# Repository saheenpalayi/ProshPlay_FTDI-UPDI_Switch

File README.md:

# ProshPlay_FTDI-UPDI_Switch
## Overview
 I made this breakout board to program the Avr 1 series chips like attiny1614, attiny412. This design have the feature to switch between the FTDI (UART) and UPDI Programming Mods with the help of a FTDI USB to TTL Serial Converter Adapter Module, Checkout the [ProshPlay_CH340G_Type-C_FTDI_Converter](https://github.com/saheenpalayi/ProshPlay_CH340G_Type-C_FTDI_Converter) that I used in this project 

## Schematic

## PCB

## Fabrication

## Testing

Refrences and Links

 - [Arduino Forum - Uploading Program to ATTiny 1616 via Serial UPDI and CH340 programmer](https://forum.arduino.cc/t/uploading-program-to-attiny-1616-via-serial-updi-and-ch340-programmer/1261787)

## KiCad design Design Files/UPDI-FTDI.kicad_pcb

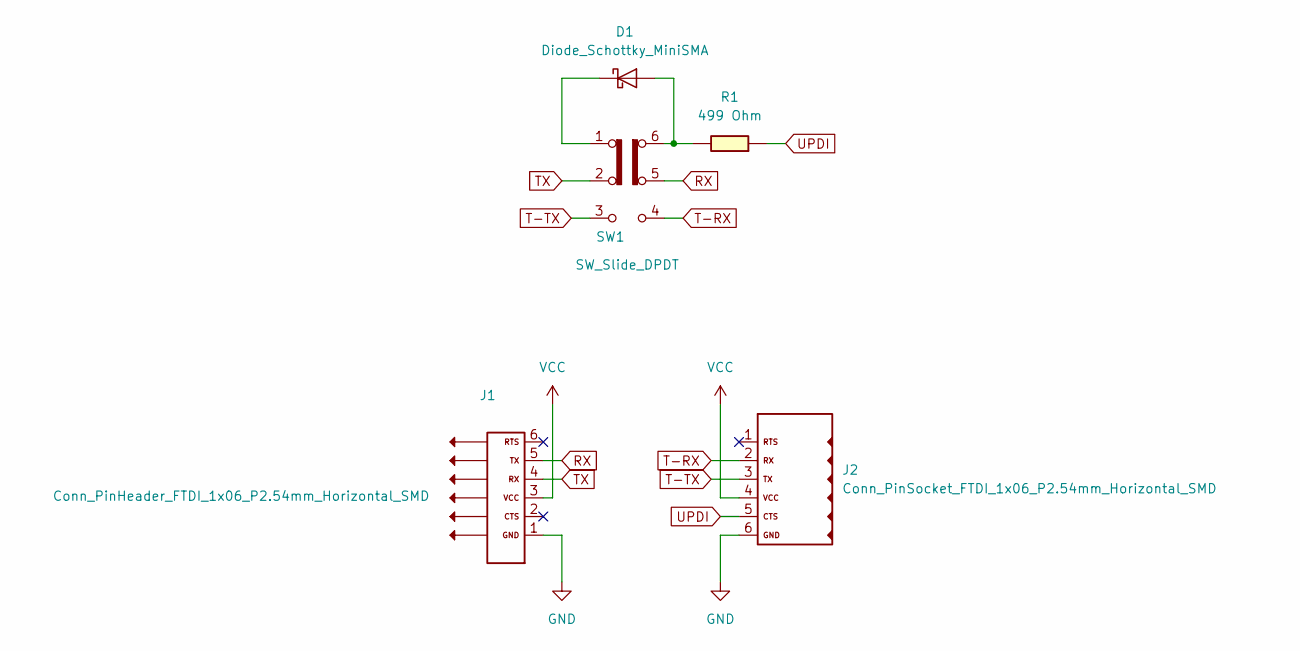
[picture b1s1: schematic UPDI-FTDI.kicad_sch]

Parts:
D1: Diode_Schottky_MiniSMA
J1: Conn_PinHeader_FTDI_1x06_P2.54mm_Horizontal_SMD; PinHeader_1x06_P2.54mm_Horizontal_SMD
J2: Conn_PinSocket_FTDI_1x06_P2.54mm_Horizontal_SMD; PinSocket_1x06_P2.54mm_Horizontal_SMD
R1: 499 Ohm; R_1206
SW1: SW_Slide_DPDT; SW_JS202011SCQN

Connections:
GND: J1.1, J2.6
unnamed: D1.2 (A), R1.1, SW1.6 (C)
unnamed: D1.1 (K), SW1.1 (A)
RX: J1.5, SW1.5 (B)
T-RX: J2.2, SW1.4 (A)
T-TX: J2.3, SW1.3 (C)
TX: J1.4, SW1.2 (B)
UPDI: J2.5, R1.2
VCC: J1.3, J2.4

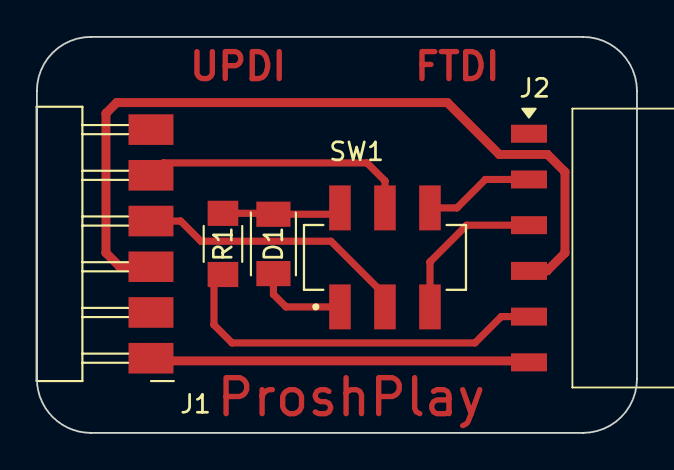
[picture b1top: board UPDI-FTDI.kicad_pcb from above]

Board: 2 copper layers, 33.3 x 22.0 mm, 5 parts (0 on the bottom side), 9 nets.

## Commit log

2025-03-26 updated the readme
